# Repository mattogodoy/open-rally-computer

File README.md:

# Open Rally Computer

An open source tripmaster for navigation rallies

## Description

The Open Rally Computer (previously known as [Baja Pro](https://baja.matto.io/)) is a complete tripmaster for navigation rallies.

Some of its features are:

- Based on GPS technology
- Adjustable partial distance odometer
- Total distance odometer
- Speedometer
- Average speed
- Max speed
- Trip time
- Compass (CAP heading)
- Multiple languages and unit systems
- Firmware updates over-the-air

The main goal of this project is to achieve a widely used open-source device that can be improved over time by ourselves, the pilots behind the roadbook.

You can read a detailed writeup of the project here:

- [English version](https://matto.io/open-sourcing-the-baja-pro/)
- [Spanish version](https://matto.io/liberando-el-codigo-del-baja-pro/)

## Schematics and PCB

You can find all the necessary information for fabricating your own copy of the Open Rally Computer PCB in the [pcb](docs/pcb) and [schematics](docs/schematics) folders of this repository.

> **HELP NEEDED**: My knowledge in electronics is self-taught, so I'm sure there are quite a few improvements to be done in this department. If you know electronics and spot something that can be improved, please let me know by opening an issue.

- Previous models of this device have been fabricated at [JLCPCB](https://jlcpcb.com/) with great results and very good prices.
- The system I used to create the PCB was [EasyEDA](https://easyeda.com/). You can find files for the schematics and the PCB in their relative folders. There are also versions for Altium Designer.

> **HELP NEEDED**: I'd like to port these schematics and PCB to KiCad, so we continue with the open source spirit :)
>
> If you know your way around KiCad, I'd really appreciate some help porting this board.

The bill of materials is located in a CSV file in the [bom](docs/pcb/bom) folder. If you find a missing component, please report it by opening an issue.

## User manual

You can find a PDF version of the User Manual in the [manual](docs/manual) folder.

> **HELP NEEDED**: The user manual is currently only in Spanish and it still has a lot of Baja Pro branding that has to be changed to "Open Rally Computer". I'd really appreciate some help transcribing it to Markdown and translating it into other languages, being english the top priority right now.

## Getting Started

These instructions will allow you to compile the project in you local computer. In order to run it you will need an actual device.

### Prerequisites

This project has been developed using VSCode with the PlatformIO plugin, which is is the recommended setup.

- Install [VSCode](https://code.visualstudio.com/)
- Install the [PlatformIO plugin](https://platformio.org/install/ide?install=vscode)
- Clone this repository

```bash
git clone https://github.com/mattogodoy/open-rally-computer.git
```

### Building

To build this project you can open the directory of the repository you just downloaded in VSCode.

Once open, go to the sidebar at the left, PlatformIO -> esp32dev -> General -> Build

The required libraries are already bundled in the `lib` directory of this repo. PlatformIO will automatically try to use them.
If for some reason you are getting compilation errors because of missing libraries, you can always install them manually going to PlatformIO -> PIO Home -> Libraries.

You can find the list of necessary libraries in the file [platformio.ini](platformio.ini).

## Flashing into device

Once the project compiles correctly in your computer, you are ready to flash it into the rally computer.

1. Connect your ESP32 (DevKit or programmer) to your computer via USB.
2. Go to PlatformIO -> esp32dev -> General -> Upload
3. PlatformIO should automatically detect the serial port where your ESP32 is connected, buld the project and flash it for you.

## Contributing

Please read [CONTRIBUTING.md](CONTRIBUTING.md) for details on the process for submitting pull requests.

Also read [CODE_OF_CONDUCT.md](CODE_OF_CONDUCT.md) for details on the code of conduct for this project.

## Versioning

We use [SemVer](http://semver.org/) for versioning.

For a list of available versions, see the [tags on this repository](https://github.com/mattogodoy/open-rally-computer/tags).

## Authors

- **Matías Godoy** - [matto.io](https://matto.io/)

See also the list of [contributors](https://github.com/mattogodoy/open-rally-computer/graphs/contributors) who participated in this project.

## TO-DO

There are a few things I'd like to do in order to improve this project and its repository:

- [x] Build, upload and tag Version 1.0.0 binary as a release
- [x] Translate user manual to english
- [ ] Port the PCB files to KiCad
- [ ] Create proper documentation in GitHub Wiki
- [ ] Create Continuous Integration using GitHub Actions

## License

This project is licensed under the GPL v3 License - see the [LICENSE](LICENSE) file for details.

This is what this means:

1. Anyone can copy, modify and distribute this software.
2. If you do, you have to include the license and copyright notice with each and every distribution.
3. You can use this software privately.
4. You can use this software for commercial purposes.
5. If you build your business based on this code, you have to open-source your whole code base.
6. Any modifications of this code base MUST be distributed with the same license (GPL v3).
7. Any changes made to this code MUST be indicated on distribution.
8. This software is provided without warranty.
9. The software author or license can not be held liable for any damages inflicted by the software.

## Changelog

- **1.0.0**: Initial version
  - The complete project was open sourced, including source code, bill of materials, PCB desings and user manual.

## Contributors

- [turtle3333](https://github.com/turtle3333): User manual translation

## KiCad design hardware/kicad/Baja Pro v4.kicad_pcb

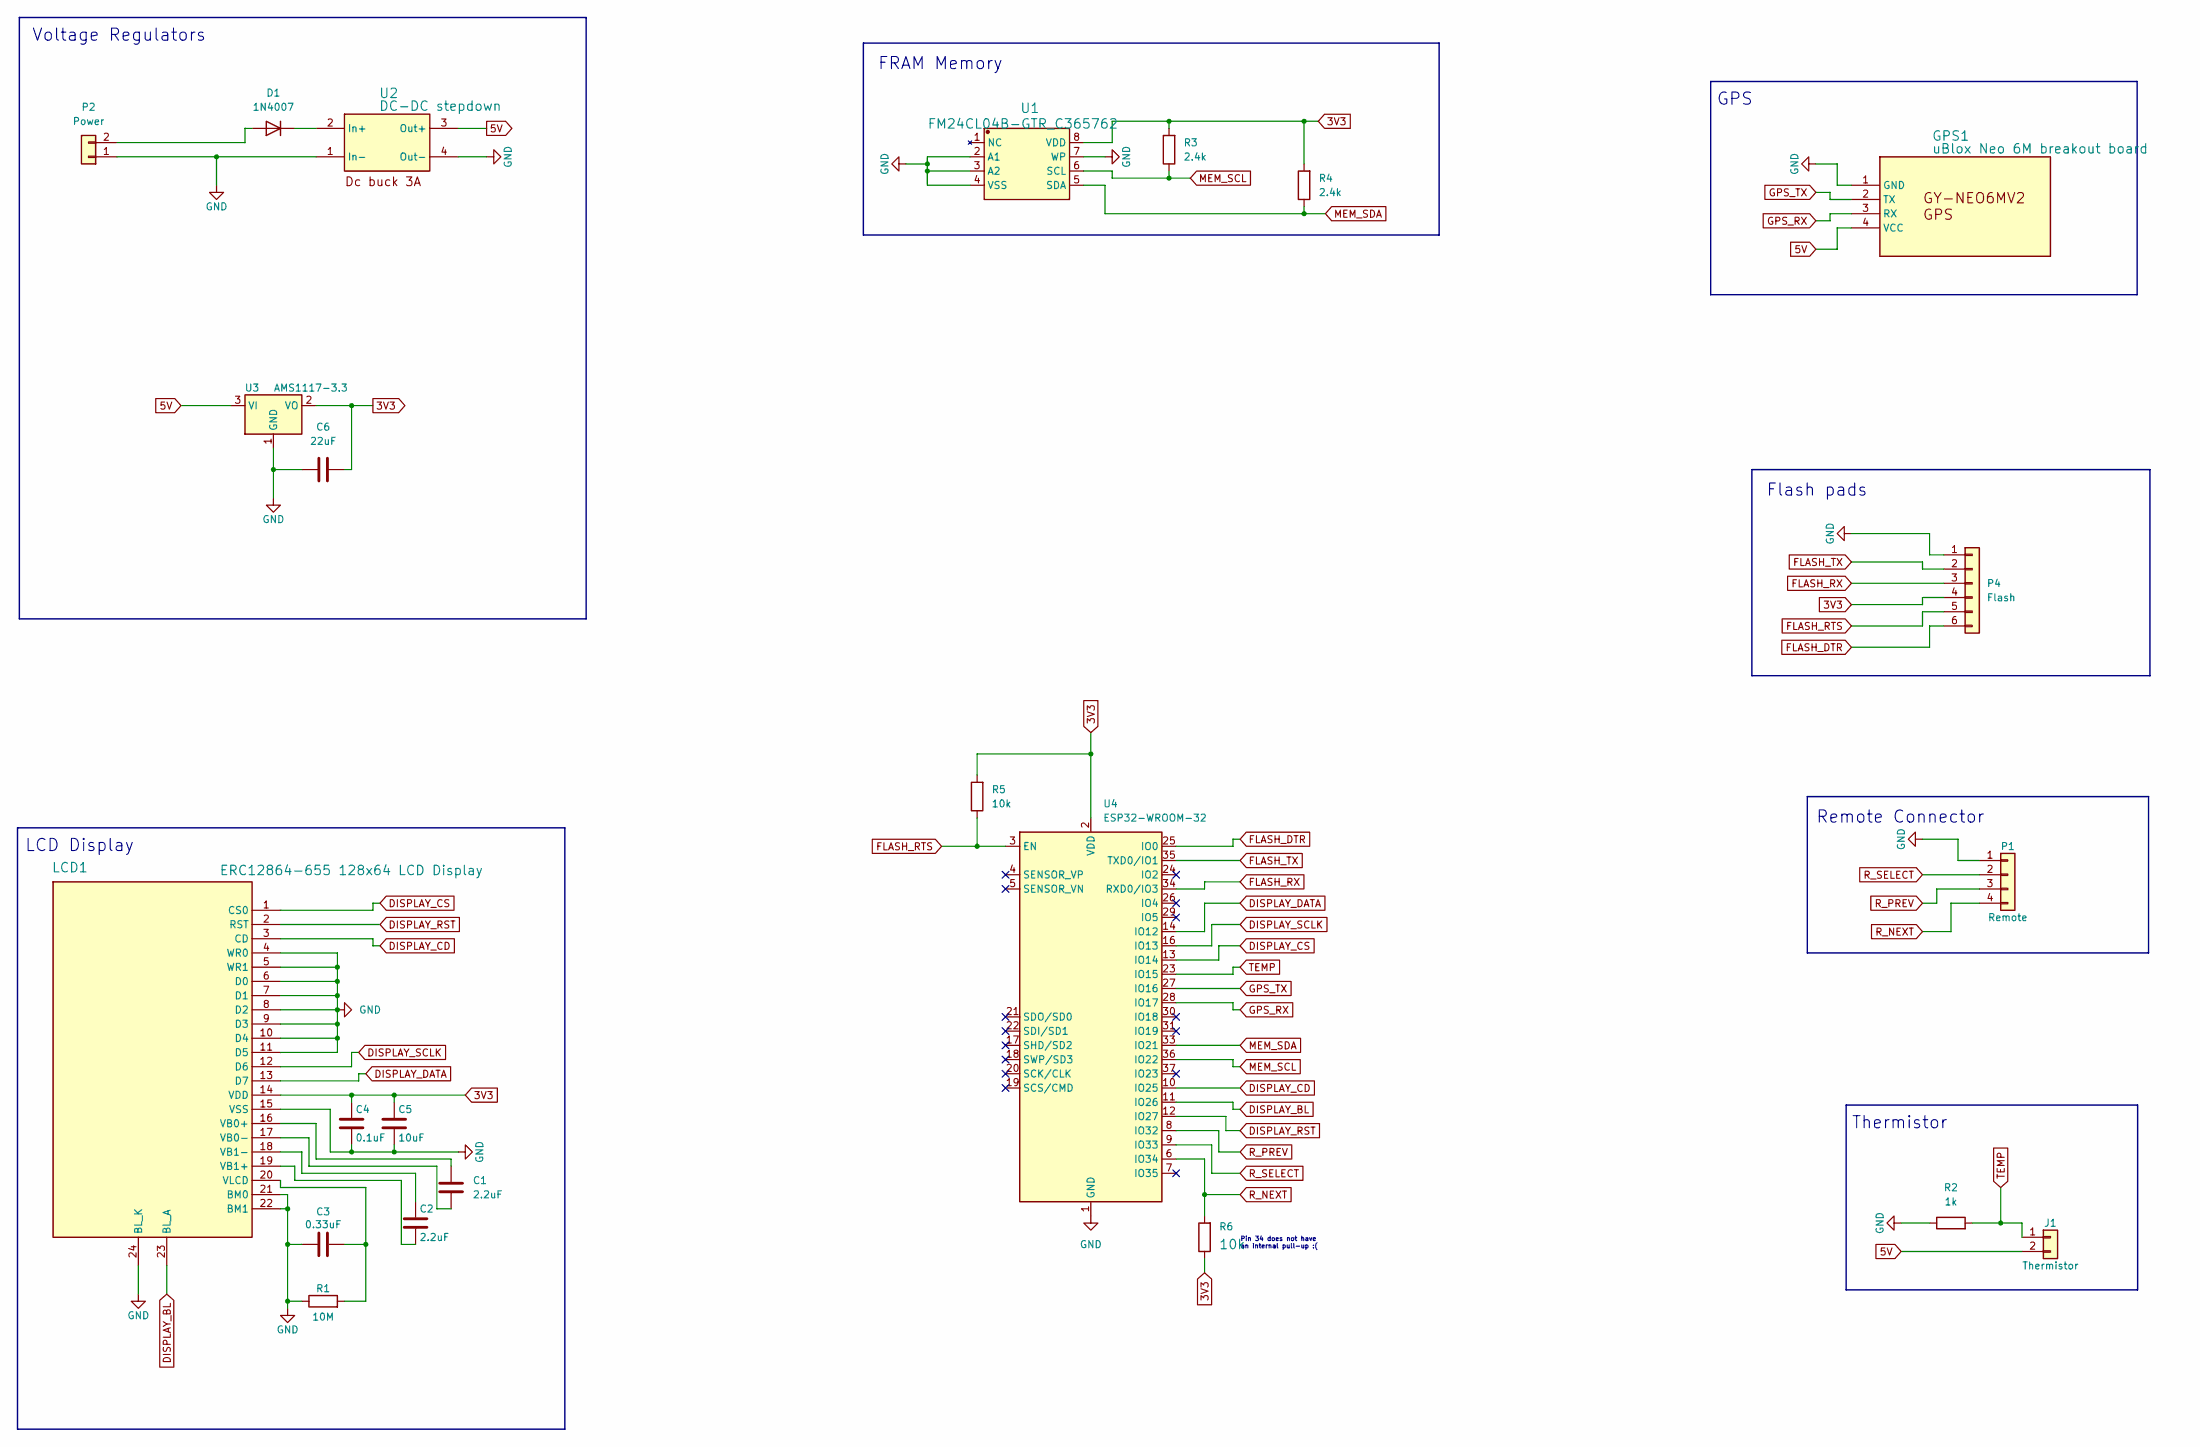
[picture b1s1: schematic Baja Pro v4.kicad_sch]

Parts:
C1, C2: 2.2uF; 1206
C3: 0.33uF; 1206
C4: 0.1uF; 1206
C5: 10uF; 1206
C6: 22uF; 1206; Manufacturer Part 1206B226K160NT
D1: 1N4007; D_SOD-123F
GPS1: uBlox Neo 6M breakout board; GY-NEO6MV2; Manufacturer Part GY-NEO6MV2
J1: Thermistor; PinHeader_1x02_P2.54mm_Vertical
LCD1: ERC12864-655 128x64 LCD Display; ERC12864-655; Manufacturer Part ERC12864-655
P1: Remote; PinHeader_1x04_P2.54mm_Vertical
P2: Power; PinHeader_1x02_P2.54mm_Vertical
P4: Flash; PinHeader_1x06_P2.54mm_Vertical
R1: 10M; 1206
R2: 1k; 1206
R3, R4: 2.4k; 1206
R5, R6: 10k; 1206
U1: FM24CL04B-GTR_C365762; SOIC-8_150MIL; Manufacturer Part FM24CL04B-GTR
U2: DC-DC stepdown; DC-DC STEPDOWN; Manufacturer Part ?
U3: AMS1117-3.3; SOT-223-3_TabPin2
U4: ESP32-WROOM-32

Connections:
3V3: C4.1, C5.1, C6.2, LCD1.14 (VDD), P4.4, R3.2, R4.2, R5.2, R6.1, U1.8 (VDD), U3.2 (VO), U4.2 (VDD)
5V: GPS1.4 (VCC), J1.2, U2.3 (Out+), U3.3 (VI)
DISPLAY_BL: LCD1.23 (BL_A), U4.11 (IO26)
DISPLAY_CD: LCD1.3 (CD), U4.10 (IO25)
DISPLAY_CS: LCD1.1 (CS0), U4.13 (IO14)
DISPLAY_DATA: LCD1.13 (D7), U4.14 (IO12)
DISPLAY_RST: LCD1.2 (RST), U4.12 (IO27)
DISPLAY_SCLK: LCD1.12 (D6), U4.16 (IO13)
FLASH_DTR: P4.6, U4.25 (IO0)
FLASH_RTS: P4.5, R5.1, U4.3 (EN)
FLASH_RX: P4.3, U4.34 (RXD0/IO3)
FLASH_TX: P4.2, U4.35 (TXD0/IO1)
GND: C3.1, C4.2, C5.2, C6.1, GPS1.1 (GND), LCD1.4 (WR0), LCD1.5 (WR1), LCD1.6 (D0), LCD1.7 (D1), LCD1.8 (D2), LCD1.9 (D3), LCD1.10 (D4), LCD1.11 (D5), LCD1.15 (VSS), LCD1.21 (BM0), LCD1.22 (BM1), LCD1.24 (BL_K), P1.1, P2.1, P4.1, R1.1, R2.1, U1.2 (A1), U1.3 (A2), U1.4 (VSS), U1.7 (WP), U2.1 (In-), U2.4 (Out-), U3.1 (GND), U4.1 (GND), U4.15 (GND), U4.38 (GND), U4.39 (GND)
GPS_RX: GPS1.3 (RX), U4.28 (IO17)
GPS_TX: GPS1.2 (TX), U4.27 (IO16)
MEM_SCL: R3.1, U1.6 (SCL), U4.36 (IO22)
MEM_SDA: R4.1, U1.5 (SDA), U4.33 (IO21)
unnamed: D1.2 (A), P2.2
unnamed: D1.1 (K), U2.2 (In+)
unnamed: C1.2, LCD1.16 (VB0+)
unnamed: C1.1, LCD1.17 (VB0-)
unnamed: C2.2, LCD1.19 (VB1+)
unnamed: C2.1, LCD1.18 (VB1-)
unnamed: C3.2, LCD1.20 (VLCD), R1.2
R_NEXT: P1.4, R6.2, U4.6 (IO34)
R_PREV: P1.3, U4.8 (IO32)
R_SELECT: P1.2, U4.9 (IO33)
TEMP: J1.1, R2.2, U4.23 (IO15)

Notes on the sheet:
FRAM Memory
Thermistor
GPS
Pin 34 does not have an internal pull-up :(
Flash pads
Voltage Regulators
LCD Display
Remote Connector

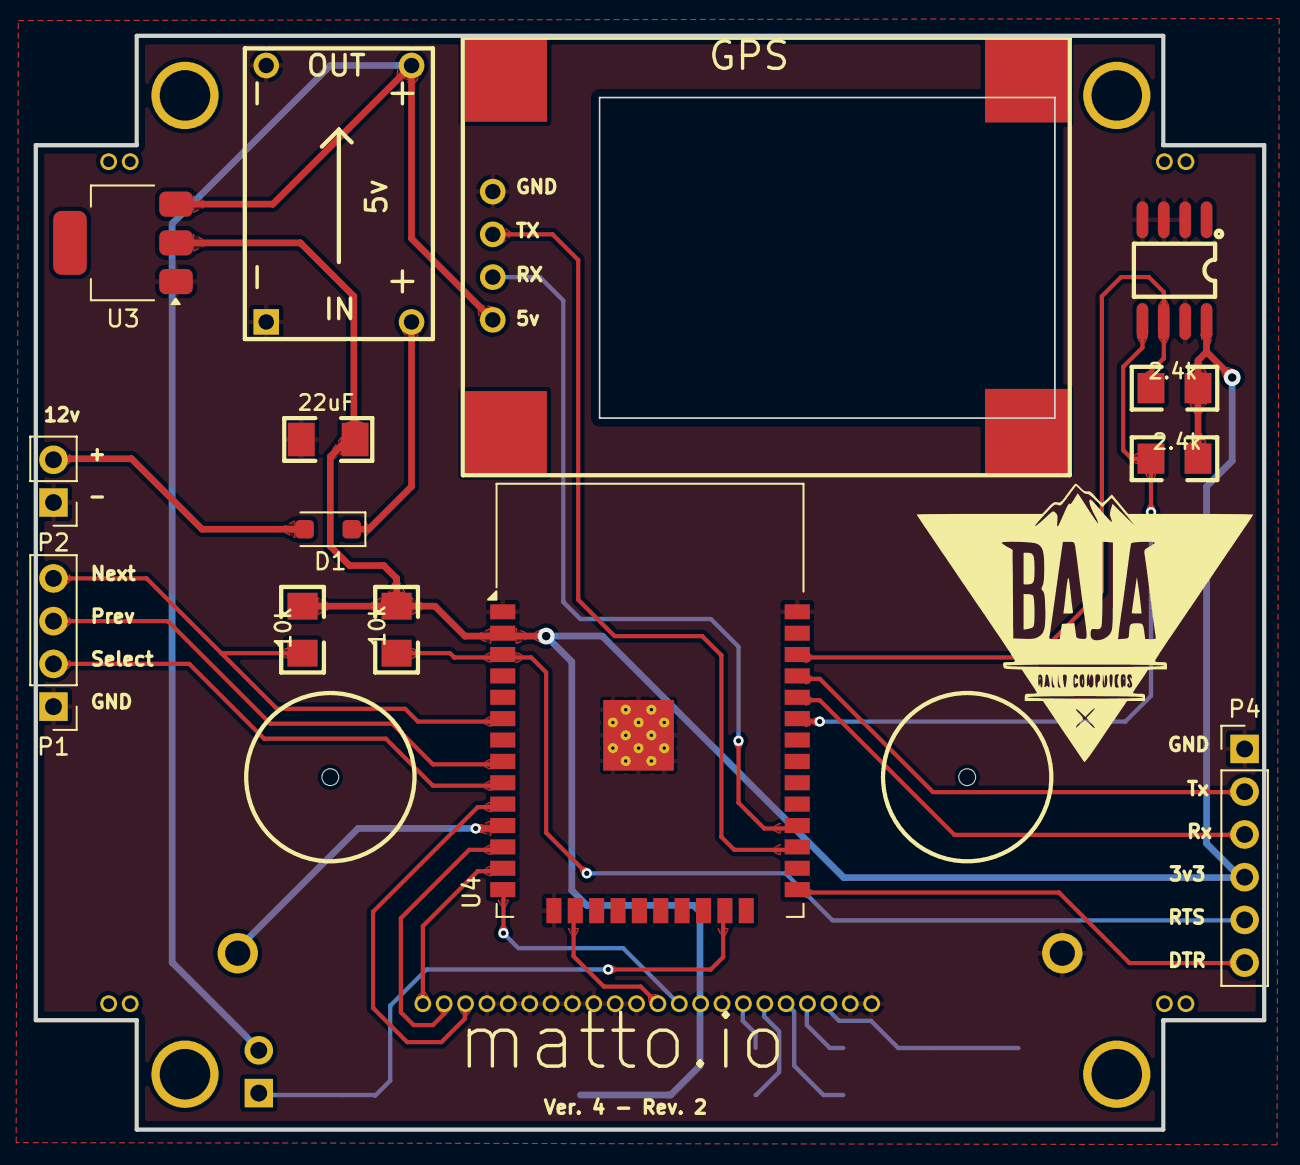
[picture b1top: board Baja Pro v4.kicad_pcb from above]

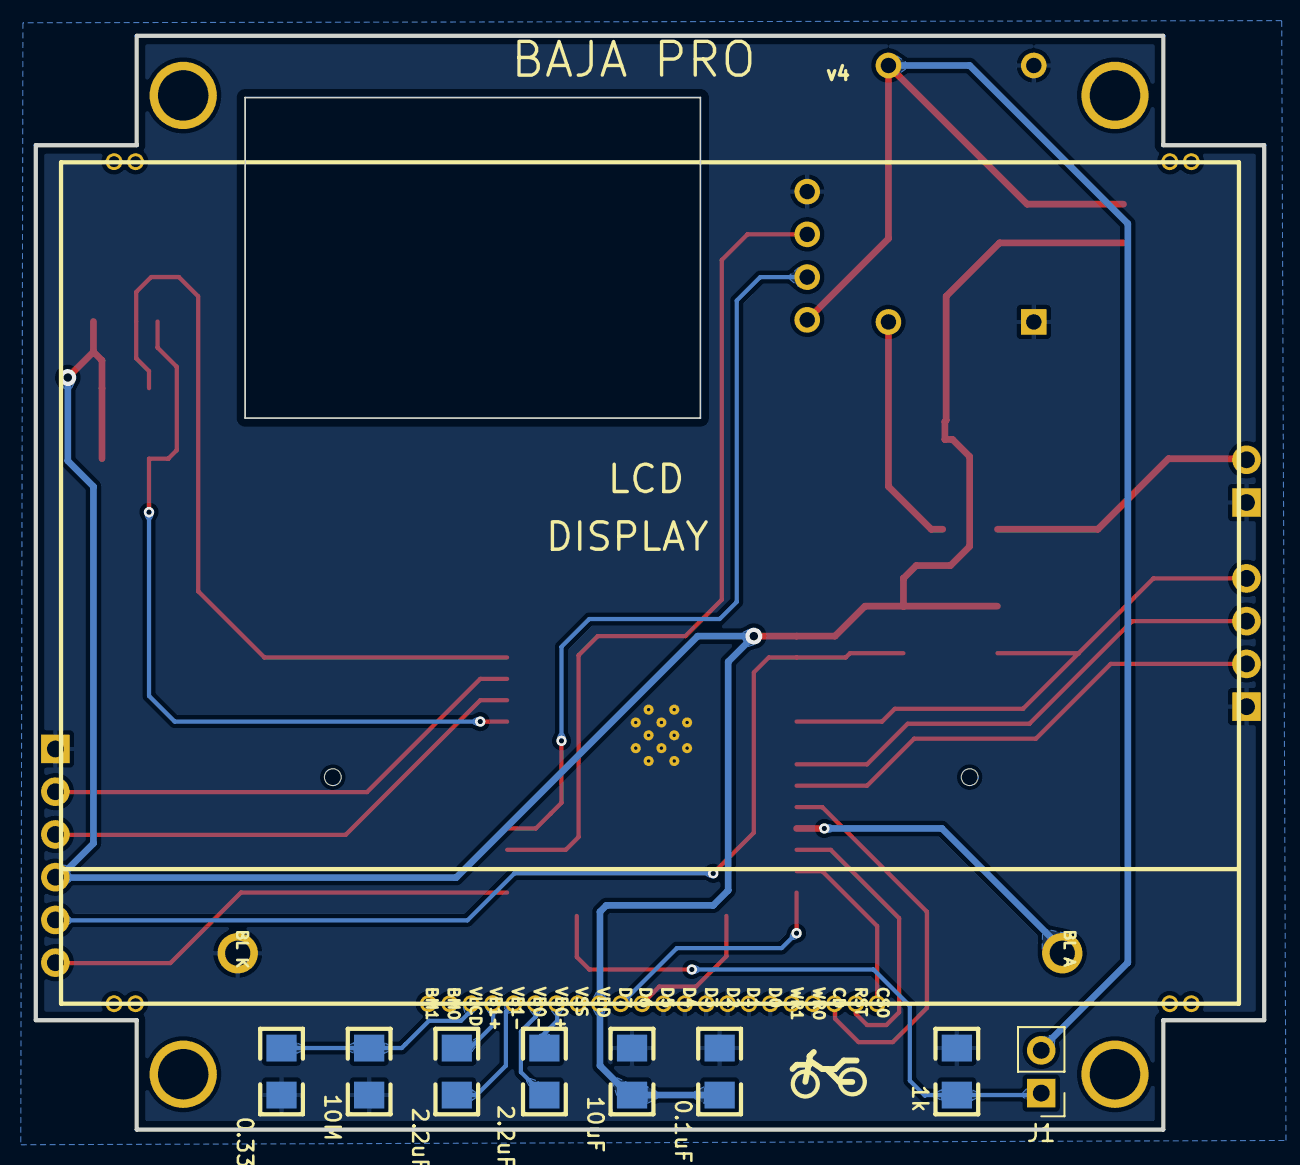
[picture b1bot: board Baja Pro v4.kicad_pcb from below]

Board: 2 copper layers, 73.0 x 65.0 mm, 29 parts (9 on the bottom side), 28 nets.

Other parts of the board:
Hole_gge526: Hole_gge526
Hole_gge527: Hole_gge527
Pad_gge522: Pad_gge522
Pad_gge523: Pad_gge523
Pad_gge524: Pad_gge524
Pad_gge525: Pad_gge525

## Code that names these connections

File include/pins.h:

// Open Rally Computer
// Copyright (C) 2021  Matías Godoy

// This program is free software: you can redistribute it and/or modify
// it under the terms of the GNU General Public License as published by
// the Free Software Foundation, either version 3 of the License, or
// (at your option) any later version.

// This program is distributed in the hope that it will be useful,
// but WITHOUT ANY WARRANTY; without even the implied warranty of
// MERCHANTABILITY or FITNESS FOR A PARTICULAR PURPOSE. See the
// GNU General Public License for more details.

// You should have received a copy of the GNU General Public License
// along with this program. If not, see <http://www.gnu.org/licenses/>.


#pragma once

#define PIN_DISPLAY_CLOCK     13
#define PIN_DISPLAY_DATA      12
#define PIN_DISPLAY_CS        14
#define PIN_DISPLAY_DC        25
#define PIN_DISPLAY_RESET     27
#define PIN_BUTTON_PREV       32
#define PIN_BUTTON_SELECT     33
#define PIN_BUTTON_NEXT       34
#define PIN_BACKLIGHT         26
#define PIN_GPS_RX            16
#define PIN_GPS_TX            17
#define PIN_THERMISTOR        15

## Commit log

2021-11-10 Update README.md
    Added links to blog post
2021-11-10 Update README.md
    Updated to-do list
2021-11-17 Initial English User Manual
    PDF user manual converted to English and markdown
2021-11-19 Update README.md
    Added contributors section
2022-06-12 Added compatible GPS modules
